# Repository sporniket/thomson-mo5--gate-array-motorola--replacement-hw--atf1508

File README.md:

# Replacement of the Motorola gate array for the Thomson MO5 by Microchip ATF1508

> [WARNING] Please read carefully this note before using this project. It contains important facts.

Content

1. What is **Replacement of the Motorola gate array for the Thomson MO5 by Microchip ATF1508**, and when to use it ?
2. What should you know before using **Replacement of the Motorola gate array for the Thomson MO5 by Microchip ATF1508** ?
3. How to use **Replacement of the Motorola gate array for the Thomson MO5 by Microchip ATF1508** ?
4. Known issues
5. Miscellanous

## 1. What is **Replacement of the Motorola gate array for the Thomson MO5 by Microchip ATF1508**, and when to use it ?

**Replacement of the Motorola gate array for the Thomson MO5 by Microchip ATF1508** is a hardware project to replace the original Motorola Gate Array of the Thomson MO5 8-bit computer, using an ATF1508.

### Licence

**Replacement of the Motorola gate array for the Thomson MO5 by Microchip ATF1508** is published under the Creative Commons CC0 license. You can find a copy of the licence there : https://creativecommons.org/publicdomain/zero/1.0/legalcode

You can copy, modify, distribute and perform the work, even for commercial purposes, all without asking permission.

**Replacement of the Motorola gate array for the Thomson MO5 by Microchip ATF1508** is distributed in the hope that it will be useful, but WITHOUT ANY WARRANTY; without even the implied warranty of MERCHANTABILITY or FITNESS FOR A PARTICULAR PURPOSE.

### Release notes

#### Version 1.0.0

Initial release.

> Note : I did something with the 2×4 header connector footprint, believing that it would held better the connector, but it does not help at all, sorry. I will fix this when I have time, it is just a bit inconvenient.

## 2. What should you know before using **Replacement of the Motorola gate array for the Thomson MO5 by Microchip ATF1508** ?

**Replacement of the Motorola gate array for the Thomson MO5 by Microchip ATF1508** is made using Kicad.

> Do not use **Replacement of the Motorola gate array for the Thomson MO5 by Microchip ATF1508** if this project is not suitable for your project.

### Fusemap file to program the ATF1508

You will find the SVF file in the `fusemap` folder.

### Bill Of Material (BOM)

|Item|Quantity|Designators|Type|Reference|Manufacturer|Link|
|---|---|---|---|---|---|---|
|1|8|`C1`, `C2`, `C3`, `C4`, `C5`, `C6`, `C7`, `C8`|Capacitor 0.22uF SMD 0603|220nF 25VDC 0603|N/A|[lcsc](https://lcsc.com/product-detail/Multilayer-Ceramic-Capacitors-MLCC-SMD-SMT_YAGEO-CC0603JRX7R8BB224_C519574.html) [rs-particuliers](https://rs-particuliers.com/Product.aspx?Product=485771)|
|2|1|`J1`|Pin header 2×4 pitch 100 mils||N/A|[lcsc](https://lcsc.com/product-detail/Pin-Headers_Megastar-ZX-PZ2-54-2-4PZZ_C7501275.html)|
|3|1|`J2`|Pin stripes 9 pins and 8 pins, pitch 100 mils||N/A|[lcsc 9 pins](https://lcsc.com/product-detail/Pin-Headers_HCTL-PZ254-1-09-Z-C_C5156436.html) [lcsc 8 pins](https://lcsc.com/product-detail/Pin-Headers_HCTL-PZ254-1-08-Z-C_C5156435.html)|
|4|1|`J3`|Pin header 2×1 pitch 100 mils||N/A|[lcsc](https://lcsc.com/product-detail/Pin-Headers_XFCN-PZ254V-11-02P_C492401.html)|
|5|3|`R1`, `R2`, `R3`|Resistor 4K7 SMD 0603|Resistor Thick Film 0603 1% 4k7|N/A|[lcsc](https://lcsc.com/product-detail/Chip-Resistor-Surface-Mount_VISHAY-RCS06034K70FKEA_C2078630.html) [rs-particuliers](https://rs-particuliers.com/Product.aspx?Product=2432188)|
|6|1|`U1`|CPLD ATF1508AS|ATF1508AS-10AU100|Microchip|[lcsc](https://lcsc.com/product-detail/Programmable-Logic-Device-CPLDs-FPGAs_MICROCHIP-ATF1508AS-10AU100_C31179.html) [rs-particuliers](https://rs-particuliers.com/Product.aspx?Product=1773660)|

## 3. How to use **Replacement of the Motorola gate array for the Thomson MO5 by Microchip ATF1508** ?

### From sources

To get the latest available work, one must clone the git repository, build and install the package.

	git clone https://github.com/sporniket/thomson-mo5--gate-array-motorola--replacement-hw--atf1508.git

Then, open the project with Kicad.

## 4. Known issues
See the [project issues](https://github.com/sporniket/thomson-mo5--gate-array-motorola--replacement-hw--atf1508/issues) page.

## 5. Miscellanous

### Report issues
Use the [project issues](https://github.com/sporniket/thomson-mo5--gate-array-motorola--replacement-hw--atf1508/issues) page.

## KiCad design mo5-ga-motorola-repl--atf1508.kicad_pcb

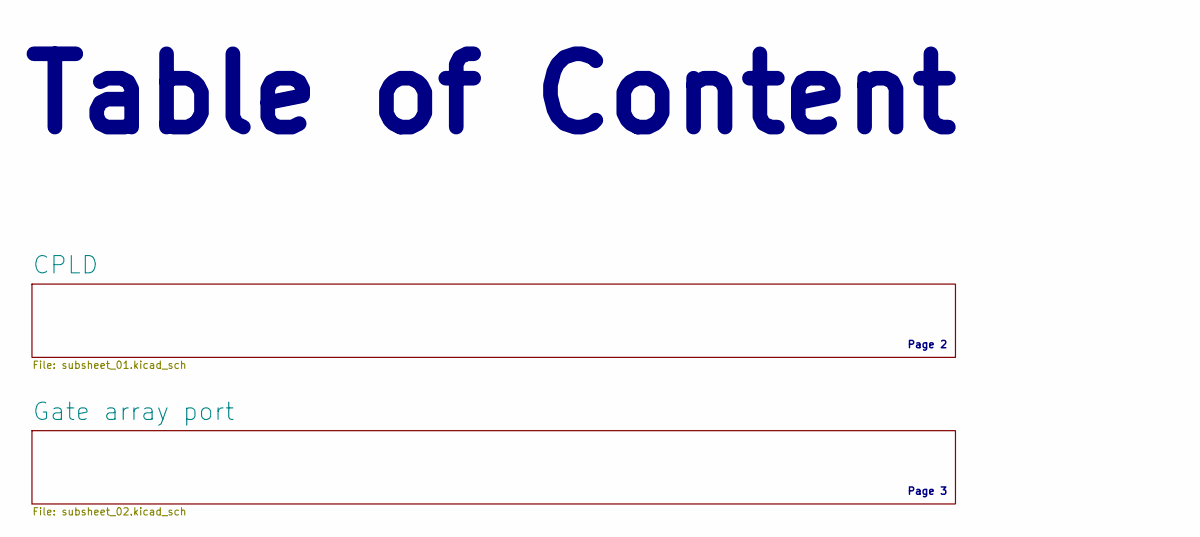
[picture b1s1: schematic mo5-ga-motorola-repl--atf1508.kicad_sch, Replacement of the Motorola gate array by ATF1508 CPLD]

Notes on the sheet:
Page 3
Page 2
Table of Content

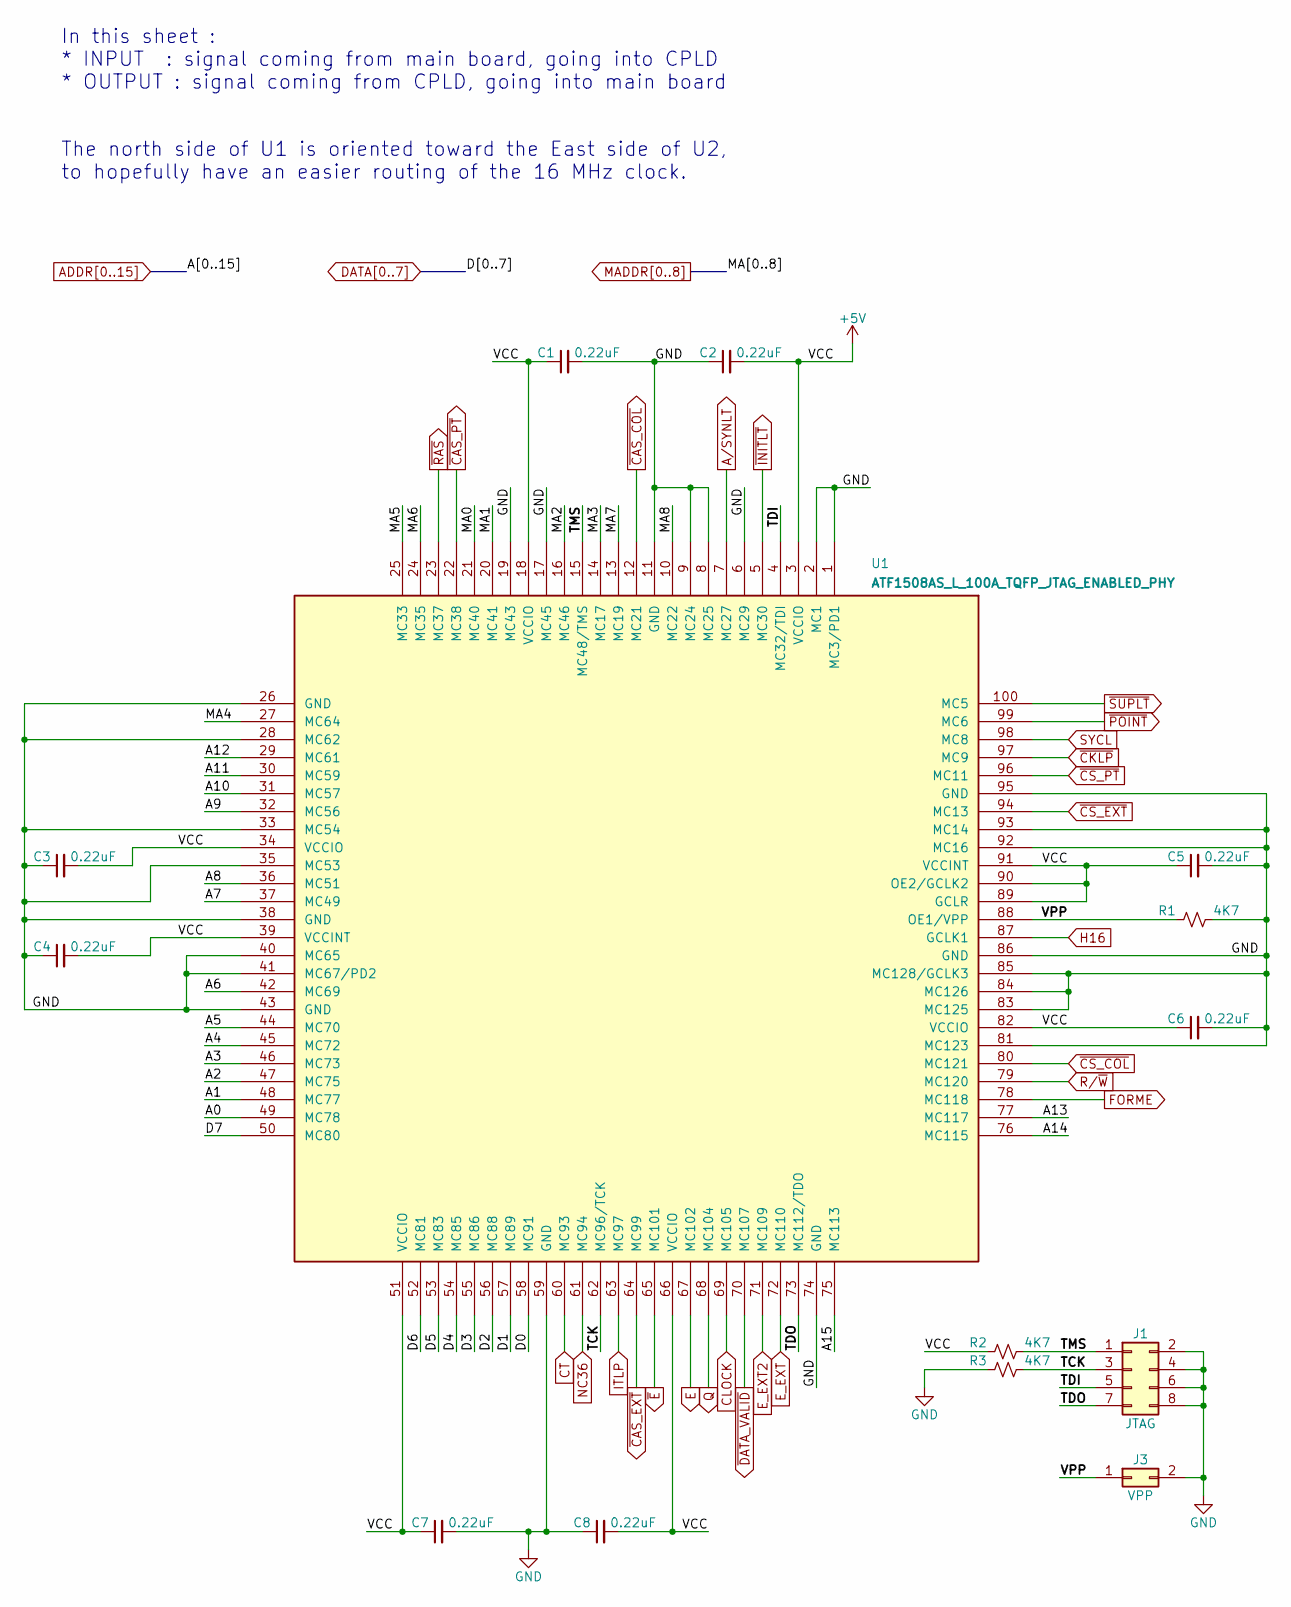
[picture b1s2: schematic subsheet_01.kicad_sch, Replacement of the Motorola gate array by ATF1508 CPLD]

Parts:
C1, C2, C3, C4, C5, C6, C7, C8: 0.22uF; C_0603_1608Metric_Pad1.08x0.95mm_HandSolder
J1: JTAG; PinHeader_2x04_P2.54mm_Vertical
J3: VPP; PinHeader_2x01_P2.54mm_Vertical
R1, R2, R3: 4K7; R_0603_1608Metric_Pad0.98x0.95mm_HandSolder
U1: ATF1508AS_L_100A_TQFP_JTAG_ENABLED_PHY; TQFP-100_14x14mm_P0.5mm

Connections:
+5V: C1.1, C2.2, C3.2, C4.2, C5.1, C6.1, C7.1, C8.2, R2.1, U1.3 (VCCIO), U1.18 (VCCIO), U1.34 (VCCIO), U1.39 (VCCINT), U1.51 (VCCIO), U1.66 (VCCIO), U1.82 (VCCIO), U1.89 (GCLR), U1.90 (OE2/GCLK2), U1.91 (VCCINT); also elsewhere on the board
/CPLD/TCK: J1.3, R3.2, U1.62 (MC96/TCK)
/CPLD/TDI: J1.5, U1.4 (MC32/TDI)
/CPLD/TDO: J1.7, U1.73 (MC112/TDO)
/CPLD/TMS: J1.1, R2.2, U1.15 (MC48/TMS)
/CPLD/VPP: J3.1, R1.1, U1.88 (OE1/VPP)
ADDR0: U1.49 (MC78); also elsewhere on the board
ADDR1: U1.48 (MC77); also elsewhere on the board
ADDR2: U1.47 (MC75); also elsewhere on the board
ADDR3: U1.46 (MC73); also elsewhere on the board
ADDR4: U1.45 (MC72); also elsewhere on the board
ADDR5: U1.44 (MC70); also elsewhere on the board
ADDR6: U1.42 (MC69); also elsewhere on the board
ADDR7: U1.37 (MC49); also elsewhere on the board
ADDR8: U1.36 (MC51); also elsewhere on the board
ADDR9: U1.32 (MC56); also elsewhere on the board
ADDR10: U1.31 (MC57); also elsewhere on the board
ADDR11: U1.30 (MC59); also elsewhere on the board
ADDR12: U1.29 (MC61); also elsewhere on the board
ADDR13: U1.77 (MC117); also elsewhere on the board
ADDR14: U1.76 (MC115); also elsewhere on the board
ADDR15: U1.75 (MC113); also elsewhere on the board
A/SYNLT: U1.7 (MC27); also elsewhere on the board
CLOCK: U1.69 (MC105); also elsewhere on the board
CT: U1.60 (MC93); also elsewhere on the board
DATA0: U1.58 (MC91); also elsewhere on the board
DATA1: U1.57 (MC89); also elsewhere on the board
DATA2: U1.56 (MC88); also elsewhere on the board
DATA3: U1.55 (MC86); also elsewhere on the board
DATA4: U1.54 (MC85); also elsewhere on the board
DATA5: U1.53 (MC83); also elsewhere on the board
DATA6: U1.52 (MC81); also elsewhere on the board
DATA7: U1.50 (MC80); also elsewhere on the board
E: U1.67 (MC102); also elsewhere on the board
E_EXT: U1.72 (MC110); also elsewhere on the board
E_EXT2: U1.71 (MC109); also elsewhere on the board
FORME: U1.78 (MC118); also elsewhere on the board
GND: C1.2, C2.1, C3.1, C4.1, C5.2, C6.2, C7.2, C8.1, J1.2, J1.4, J1.6, J1.8, J3.2, R1.2, R3.1, U1.1 (MC3/PD1), U1.2 (MC1), U1.6 (MC29), U1.8 (MC25), U1.9 (MC24), U1.11 (GND), U1.17 (MC45), U1.19 (MC43), U1.26 (GND), U1.28 (MC62), U1.33 (MC54), U1.35 (MC53), U1.38 (GND), U1.40 (MC65), U1.41 (MC67/PD2), U1.43 (GND), U1.59 (GND), U1.74 (GND), U1.81 (MC123), U1.83 (MC125), U1.84 (MC126), U1.85 (MC128/GCLK3), U1.86 (GND), U1.92 (MC16), U1.93 (MC14), U1.95 (GND); also elsewhere on the board
H16: U1.87 (GCLK1); also elsewhere on the board
ITLP: U1.63 (MC97); also elsewhere on the board
MADDR0: U1.21 (MC40); also elsewhere on the board
MADDR1: U1.20 (MC41); also elsewhere on the board
MADDR2: U1.16 (MC46); also elsewhere on the board
MADDR3: U1.14 (MC17); also elsewhere on the board
MADDR4: U1.27 (MC64); also elsewhere on the board
MADDR5: U1.25 (MC33); also elsewhere on the board
MADDR6: U1.24 (MC35); also elsewhere on the board
MADDR7: U1.13 (MC19); also elsewhere on the board
MADDR8: U1.10 (MC22); also elsewhere on the board
NC36: U1.61 (MC94); also elsewhere on the board
Q: U1.68 (MC104); also elsewhere on the board
R/~W: U1.79 (MC120); also elsewhere on the board
SYCL: U1.98 (MC8); also elsewhere on the board
~CAS_COL: U1.12 (MC21); also elsewhere on the board
~CAS_EXT: U1.64 (MC99); also elsewhere on the board
~CAS_PT: U1.22 (MC38); also elsewhere on the board
~CKLP: U1.97 (MC9); also elsewhere on the board
~CS_COL: U1.80 (MC121); also elsewhere on the board
~CS_EXT: U1.94 (MC13); also elsewhere on the board
~CS_PT: U1.96 (MC11); also elsewhere on the board
~DATA_VALID: U1.70 (MC107); also elsewhere on the board
~E: U1.65 (MC101); also elsewhere on the board
~INITLT: U1.5 (MC30); also elsewhere on the board
~POINT: U1.99 (MC6); also elsewhere on the board
~RAS: U1.23 (MC37); also elsewhere on the board
~SUPLT: U1.100 (MC5); also elsewhere on the board

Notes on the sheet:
In this sheet : * INPUT : signal coming from main board, going into CPLD * OUTPUT : signal coming from CPLD, going into main board
The north side of U1 is oriented toward the East side of U2, to hopefully have an easier routing of the 16 MHz clock.

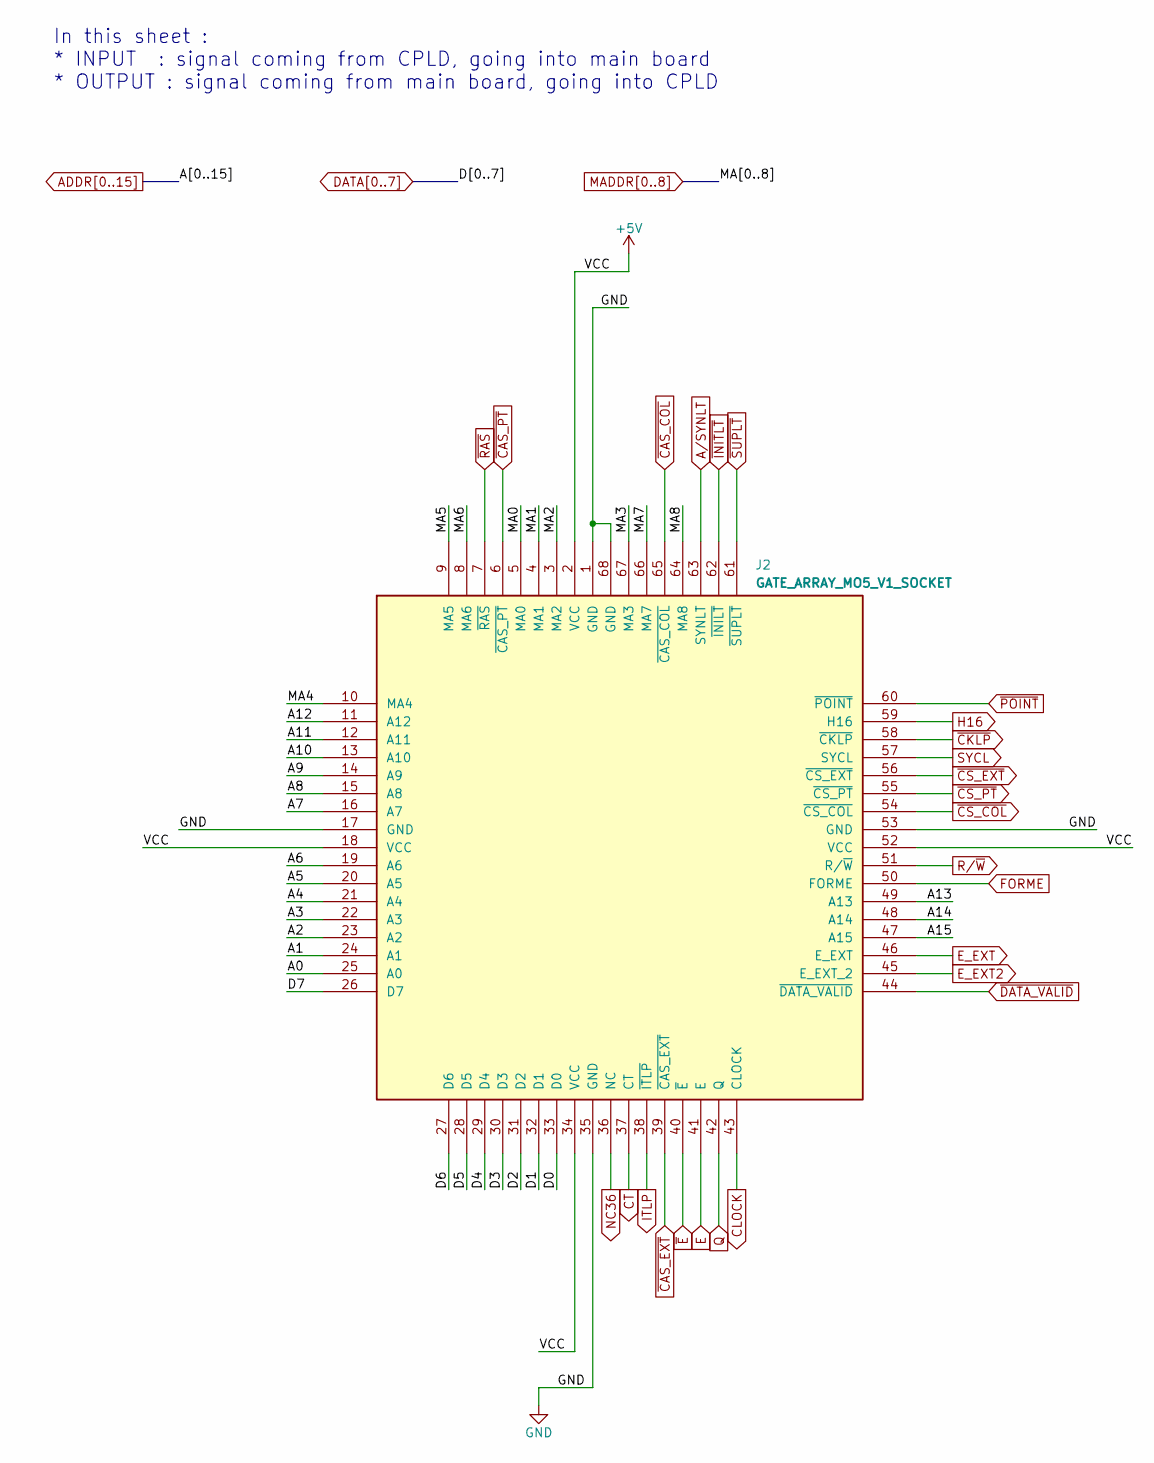
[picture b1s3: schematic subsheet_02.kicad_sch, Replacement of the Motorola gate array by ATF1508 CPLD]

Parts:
J2: GATE_ARRAY_MO5_V1_SOCKET; gate_array_plcc68_staggered

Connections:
+5V: J2.2 (VCC), J2.18 (VCC), J2.34 (VCC), J2.52 (VCC); also elsewhere on the board
ADDR0: J2.25 (A0); also elsewhere on the board
ADDR1: J2.24 (A1); also elsewhere on the board
ADDR2: J2.23 (A2); also elsewhere on the board
ADDR3: J2.22 (A3); also elsewhere on the board
ADDR4: J2.21 (A4); also elsewhere on the board
ADDR5: J2.20 (A5); also elsewhere on the board
ADDR6: J2.19 (A6); also elsewhere on the board
ADDR7: J2.16 (A7); also elsewhere on the board
ADDR8: J2.15 (A8); also elsewhere on the board
ADDR9: J2.14 (A9); also elsewhere on the board
ADDR10: J2.13 (A10); also elsewhere on the board
ADDR11: J2.12 (A11); also elsewhere on the board
ADDR12: J2.11 (A12); also elsewhere on the board
ADDR13: J2.49 (A13); also elsewhere on the board
ADDR14: J2.48 (A14); also elsewhere on the board
ADDR15: J2.47 (A15); also elsewhere on the board
A/SYNLT: J2.63 (SYNLT); also elsewhere on the board
CLOCK: J2.43 (CLOCK); also elsewhere on the board
CT: J2.37 (CT); also elsewhere on the board
DATA0: J2.33 (D0); also elsewhere on the board
DATA1: J2.32 (D1); also elsewhere on the board
DATA2: J2.31 (D2); also elsewhere on the board
DATA3: J2.30 (D3); also elsewhere on the board
DATA4: J2.29 (D4); also elsewhere on the board
DATA5: J2.28 (D5); also elsewhere on the board
DATA6: J2.27 (D6); also elsewhere on the board
DATA7: J2.26 (D7); also elsewhere on the board
E: J2.41 (E); also elsewhere on the board
E_EXT: J2.46 (E_EXT); also elsewhere on the board
E_EXT2: J2.45 (E_EXT_2); also elsewhere on the board
FORME: J2.50 (FORME); also elsewhere on the board
GND: J2.1 (GND), J2.17 (GND), J2.35 (GND), J2.53 (GND), J2.68 (GND); also elsewhere on the board
H16: J2.59 (H16); also elsewhere on the board
ITLP: J2.38 (~ITLP); also elsewhere on the board
MADDR0: J2.5 (MA0); also elsewhere on the board
MADDR1: J2.4 (MA1); also elsewhere on the board
MADDR2: J2.3 (MA2); also elsewhere on the board
MADDR3: J2.67 (MA3); also elsewhere on the board
MADDR4: J2.10 (MA4); also elsewhere on the board
MADDR5: J2.9 (MA5); also elsewhere on the board
MADDR6: J2.8 (MA6); also elsewhere on the board
MADDR7: J2.66 (MA7); also elsewhere on the board
MADDR8: J2.64 (MA8); also elsewhere on the board
NC36: J2.36 (NC); also elsewhere on the board
Q: J2.42 (Q); also elsewhere on the board
R/~W: J2.51 (R/~W); also elsewhere on the board
SYCL: J2.57 (SYCL); also elsewhere on the board
~CAS_COL: J2.65 (~CAS_COL); also elsewhere on the board
~CAS_EXT: J2.39 (~CAS_EXT); also elsewhere on the board
~CAS_PT: J2.6 (~CAS_PT); also elsewhere on the board
~CKLP: J2.58 (~CKLP); also elsewhere on the board
~CS_COL: J2.54 (~CS_COL); also elsewhere on the board
~CS_EXT: J2.56 (~CS_EXT); also elsewhere on the board
~CS_PT: J2.55 (~CS_PT); also elsewhere on the board
~DATA_VALID: J2.44 (~DATA_VALID); also elsewhere on the board
~E: J2.40 (~E); also elsewhere on the board
~INITLT: J2.62 (~INILT); also elsewhere on the board
~POINT: J2.60 (~POINT); also elsewhere on the board
~RAS: J2.7 (~RAS); also elsewhere on the board
~SUPLT: J2.61 (~SUPLT); also elsewhere on the board

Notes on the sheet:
In this sheet : * INPUT : signal coming from CPLD, going into main board * OUTPUT : signal coming from main board, going into CPLD

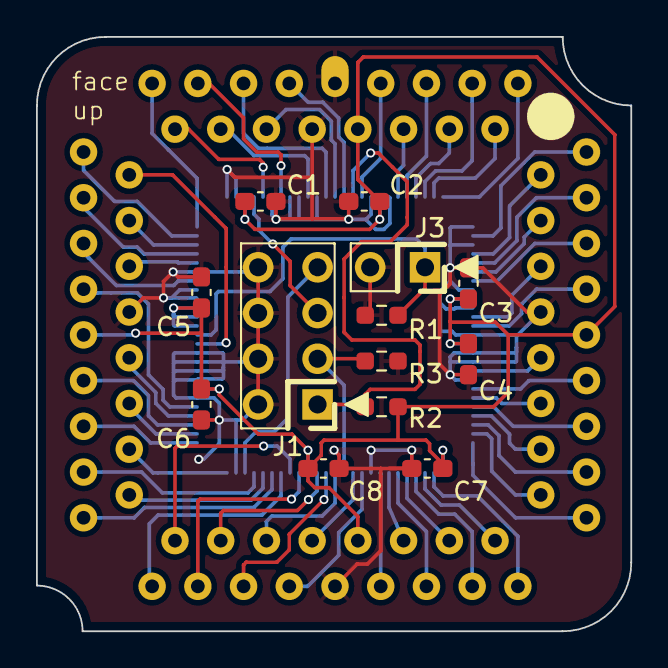
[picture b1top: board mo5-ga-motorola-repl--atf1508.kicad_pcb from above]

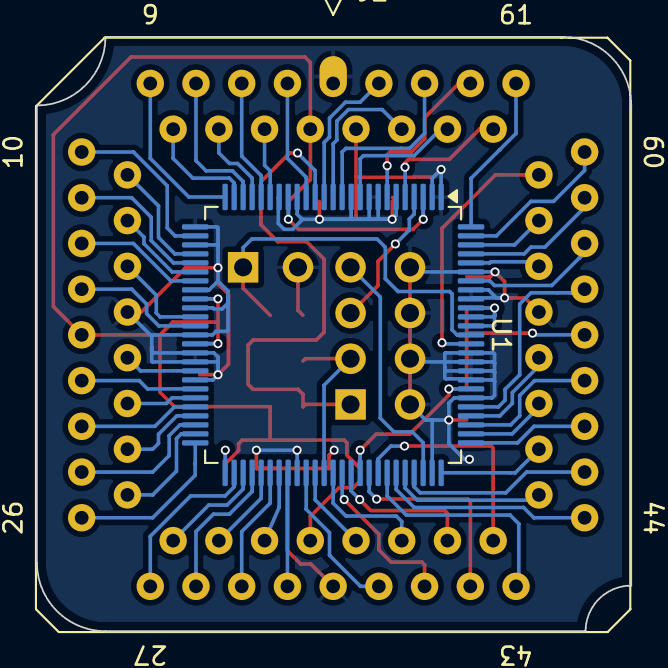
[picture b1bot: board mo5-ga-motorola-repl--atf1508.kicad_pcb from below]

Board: 4 copper layers, 33.0 x 33.0 mm, 15 parts (2 on the bottom side), 66 nets.

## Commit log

2025-05-17 Initialize the schematic : main and sub sheets, cartridge, page layout
2025-05-17 schematic : place U1 and U2, the CPLD and the Gate array connector
2025-05-17 schematic : setup all signals going through U2
2025-05-17 schematic : U2 renamed to J2
2025-05-17 schematics : put power symbols
2025-05-17 schematic : done U1, decoupling capacitors, pull resistors, JTAG and VPP connectors
2025-05-18 schematics : format text size for subsheet name in main sheet
2025-05-24 pcb : draft
2025-05-24 pcb : adjusting
2025-05-25 pcb : slowly adjusting traces
2025-05-25 pcb : adjusting traces
2025-05-31 pcb/schematics : rework connexion for easier routing, pcb edge, power distribution network
2025-07-13 prepare release
2025-07-13 tweak CI setup to remove errors caused by standard QFP footprint
2025-07-13 last save before release
2025-07-16 Put BOM in readme
2025-07-16 tweaked BOM in README for display
2025-09-21 added fusemap and some information
